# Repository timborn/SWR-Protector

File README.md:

# SWR-Protector
SWR Protection Circuit - cuts power when SWR is too high

This design is from Ron WA7GIL.
He posted it on the QRP Labs forum in early 2023.

V1.0 came back from the fab in May.  Only 2 whitewire fixes.  You
can grab the Gerber and build your own if you don't mind fixing it
when it gets back.

The whitewire changes were solved with a single change to the
schematics, so V1.1 or better of the schematics would be the one
to look at.

V2.0 now includes the "George Option", an optional alarm so you 
can hear when your radio has been shut off by the SWR Protector.

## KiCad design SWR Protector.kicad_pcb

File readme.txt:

Sun Jun 18 12:15:33 MST 2023
----------------------------

My notes to myself about problems, solutions, ideas, questions, ...

1. confirmed: I can use wire between the two BNC connectors and skip coax
2. windings on toroids are both 1:12.  On 1st toroid the center conductor
   passes through once, but then continues to 2nd toroid and loops 12x.
3. OPEN does Ron want to pick a license for this?
4. when we get to calibration step, my guess is something like
   4a. 50 Ohm dummy load, apply pwr and verify it works
   4b. 100 Ohm dummy load (2:1 SWR), apply power and tune pot until it cuts out
5. when the detector fires, the only reset is to power off / power on unit.
   TODO: I can see a need for a power switch to save the barrel plugs some wear
6. we have an LED for BadStuffHappened.  Any value in pwr LED?
7. transformers are just FT37-43 ferrite toroids
8. 1/4 watt resistors are fine. Nothing fancy; 10% tolerance or better is fine
9. Capacitors can be ordinary ceramic discs, 50 volts is sufficient 
10. "Normal" LEDs are 5mm size
11. A common ½W resistor measures about 9.2mm across, 
    while a smaller ¼W resistor is about 6.3mm long.
12. DONE: find a board size that lends itself to a box
    look for Hammond 1590 series die cast aluminum
    I don't think these die cast boxes will do.  Something with faceplates
    will be easier to drill for BNC & barrel jacks, and assemble.
    Ended up using 1593L, which has faceplates and approx size of QDX.
13. DONE: approriate mounting holes for #12 - template provided holes
14. DONE: several parts missing 3D images: barrel jack, relay, DIPs
15. DONE: barrel jack should be replaced with 2-pin variety
    ended up using 3-pin for footprint and model as Ron says that's common
15a. DONE: barrel jack has 3D model
16. DONE: consider V Refl and V Fwd test points coming out on a header
    along with +5 and GND to make micro easier to integrate.
17: RULE: PCB layout on 25 or 50 mils
    "I highly recommend you do not use a grid other than 50 mils
    or 25 mils. Otherwise, there will be tears later. All your
    components, vias, traces and board outlines must be on a 50 or
    25 mil grid. (Silkscreen is a different story)"
    - https://learn.sparkfun.com/tutorials/beginners-guide-to-kicad/all#editing-a-pcb-layout
    0.635mm = 25 mil, 1.27mm = 50 mil  
18: DONE: ground plane fill top layer
19. DONE: when you get ground plane both size add tons of vias
    Good explaination of via stiching techniques: 
    https://www.youtube.com/watch?v=Hp5ngKtl7S4
20. DONE: trace size 1mm; power net 2.5mm
    Fix: (in PCB editor)
    Edit / Select All
    Edit / Edit Track and Via Properties
    Action / Set To Specified Values / Track Width / Track: use netclass width
21. DONE: add a pair of 100 nF caps across LM78L05 +12v/gnd/+5v
22. DONE: switched power should be on same side as transceiver 
23: DONE: junction dot got huge when I added wider traces.
    Fix is File / Schematic Setup / Formatting / Junction dot size: smallest
24. DONE: what is correct placement for barrel jack on edge of board?
25. DONE: what is correct placement for BNC on edge of board?
    keep the silk screen footprint on the board.  Connector will extend out.
26. DONE: orient toroids (transformers) on edge rather than flat
    Found this in someone else's design:
    FT37-43
      <footprint>Inductor_THT:L_Toroid_Vertical_L10.0mm_W5.0mm_P5.08mm
    It only had two pads, but it might form the basis for a custom part.
27. DONE: when it's time to mfgr, review fab specs.  What's "fiducial"?
    Used for SMT, pick & place and inspection tools.
28. DONE: fix warnings about 'footprint does not match copy in library',
    but in the process I lost my 3D models for several parts.  
    Pulled them in again, but the barrel jack is not the correct part
    for those holes (TODO).
29. SOLVED/DONE - when I did a reboot for v0.8 I started with Hammond
    1593L template from DigiKey partners.
    https://github.com/Digi-Key/digikey-partner-kicad-library
    It was that template that also made changes to Board Setup that was
    causing errors with placement of TO-92 package.  DRC was complaining
    that solder mask was too close, and it was implicating the pin
    placement for a very ordinary part.

    After painstaking side-by-side comparison I observe the following 
    changes in (PCB) File / Board Setup:
    - Solder Mask/Paste 
      Solder mask expansion 0.051mm (was 0)
      Solder mask minimum web width 0.25mm (was 0) <-- this is the problem
    - Constraints
      Minimum track width 0.2mm (was 0)
      Minimum via diameter 0.4mm (was 0.5mm)
30. SOLVED/DONE - new via stitching solution.  Download a copy of plugin
    from https://github.com/jsreynaud/kicad-action-scripts
    In PCB tool Tools / External Plugins / Reveal Plugin Folder in Finder
    That's where you put the download.  There's also a Refresh option in 
    there once it's in place.  The rest is easy.  And it works.
31. Send To Fab: zip file with gerber + drill file output
32. SWR Protector BOM.ods is both BOM and cost accounting.
    I'm using Libre Office.  CSV doesn't handle formulas well, 
    and numbers doesn't like naming a cell, for some reason.
33. Git Tag each version and make sure you push tags to origin
    https://git-scm.com/book/en/v2/Git-Basics-Tagging
34. DONE: Ron thinks the power connections should be swapped, end for end, 
    so the power for radio and radio antenna connections come out the same side.
    Is this true?  He says if it's swapped, the relay won't stay triggered.
    THIS WAS ALREADY DONE somewhere between v0.5 and v0.8.  See #22 above.
35. Label the board so the ends are clear.  Everything on LED side goes 
    to radio.
36. 230617 Ron> There is still about a 1 mm gap between the DC connectors 
    and the end caps but it works like this.
    Tim> Dc shifted by 1mm. Noted
    230618 Ron> The DC connectors are close enough now to work fine with 
    the standard depth plugs. No need to move them further out unless 
    making other changes
37. Center BNC on board and make offset to barrel jack identical on both ends.
    I want to be able to create a dilling guide for the end plates.

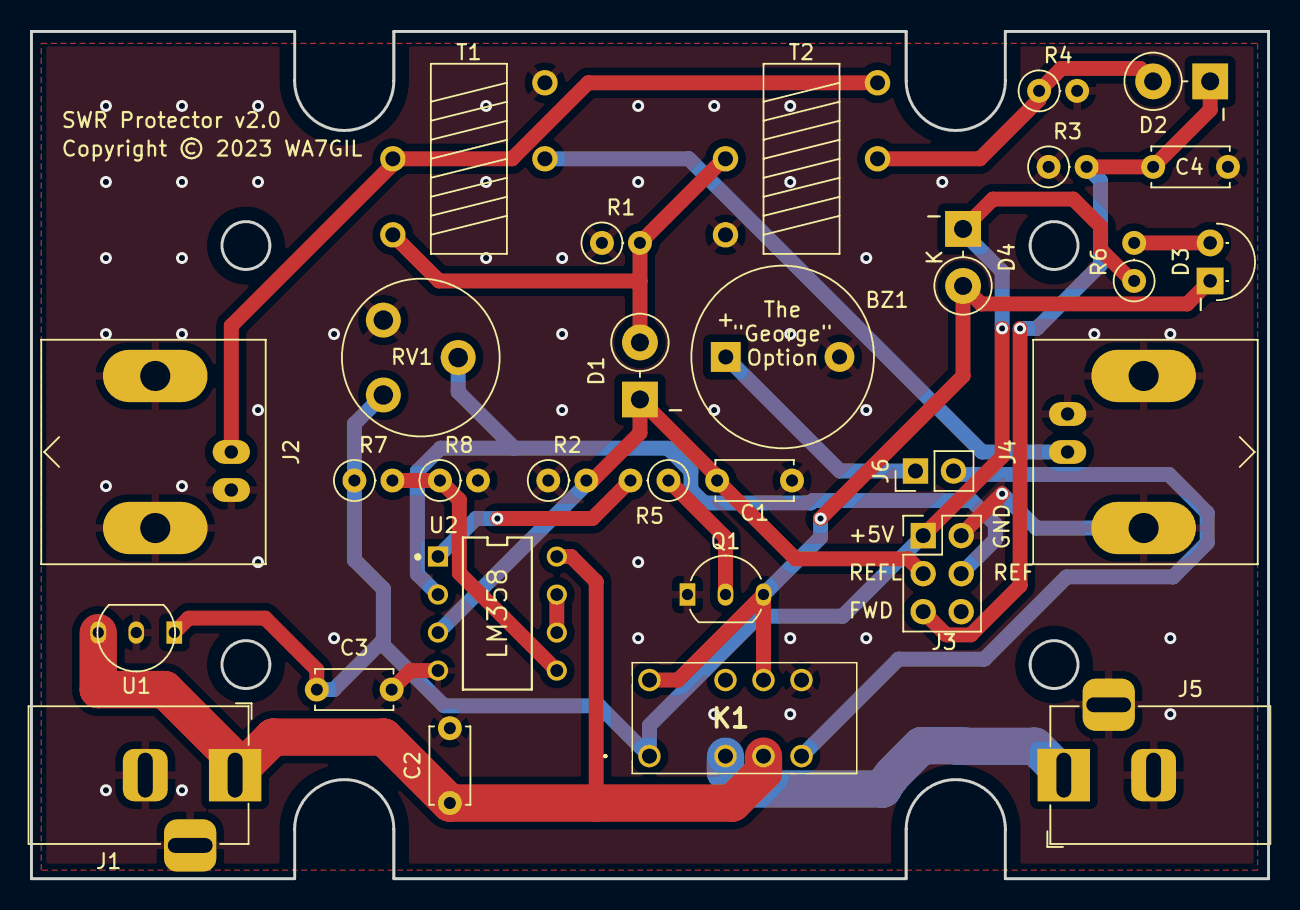
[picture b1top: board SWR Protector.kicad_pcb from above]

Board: 2 copper layers, 82.7 x 56.6 mm, 30 parts (0 on the bottom side), 19 nets.

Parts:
BZ1: Buzzer; Buzzer_12x9.5RM7.6
C1, C4: 10 nF; C_Disc_D5.0mm_W2.5mm_P5.00mm
C2, C3: 100 nF; C_Disc_D5.0mm_W2.5mm_P5.00mm
D1, D2: 1N270; D_DO-15_P3.81mm_Vertical_KathodeUp
D3: red; LED_D5.0mm_Horizontal_O1.27mm_Z9.0mm
D4: 1N4007; D_DO-15_P3.81mm_Vertical_KathodeUp
J1, J5: Barrel_Jack; BarrelJack_Horizontal
J2: antenna; BNC_Amphenol_B6252HB-NPP3G-50_Horizontal
J3: Conn_02x03; PinHeader_2x03_P2.54mm_Vertical
J4: transceiver; BNC_Amphenol_B6252HB-NPP3G-50_Horizontal
J6: Conn_01x02_Pin; PinHeader_1x02_P2.54mm_Vertical
K1: ATX209
Q1: 2N3904; TO-92_Inline
R1, R4: 51R; R_Axial_DIN0207_L6.3mm_D2.5mm_P2.54mm_Vertical
R2, R3: 100K; R_Axial_DIN0207_L6.3mm_D2.5mm_P2.54mm_Vertical
R5: 4K7; R_Axial_DIN0207_L6.3mm_D2.5mm_P2.54mm_Vertical
R6: 1K; R_Axial_DIN0207_L6.3mm_D2.5mm_P2.54mm_Vertical
R7, R8: 10K; R_Axial_DIN0207_L6.3mm_D2.5mm_P2.54mm_Vertical
RV1: 10K; Potentiometer_Piher_PT-10-V05_Vertical
T1, T2: 1:12; FT37-43-TRANSFORMER
U1: LM78L05_TO92; TO-92_Inline
U2: LM358; ON_Semiconductor-626-05-04_2015-P-MFG

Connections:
+5V: C3.1, D4.1 (K), J3.1, K1.1 (+), R6.1, R7.1, RV1.1, U1.1 (VO)
+12V: C2.1, J1.1, K1.4 (COM_1), U1.3 (VI), U2.8 (V+)
GND: BZ1.2 (+), C1.2, C2.2, C3.2, C4.2, J1.2, J1.3, J2.2 (Ext), J3.2, J4.2 (Ext), J5.2, J5.3, K1.8 (NO_2), Q1.1 (E), R1.1, R2.1, R3.1, R4.2, R8.2, RV1.3, T1.1 (AA), T2.2 (AB), U1.2 (GND), U2.4 (V-)
unnamed: BZ1.1 (-), J6.1
unnamed: D1.2 (A), R1.2, T1.2 (AB), T2.4 (SB)
unnamed: C1.1, D1.1 (K), J3.3, R2.2, U2.3 (+)
unnamed: D2.2 (A), R4.1, T2.3 (SA)
unnamed: C4.1, D2.1 (K), J3.5, R3.2
unnamed: D3.2 (A), R6.2
unnamed: D3.1 (K), D4.2 (A), K1.9 (COM_2), K1.12 (-), Q1.3 (C)
unnamed: J2.1 (In), T1.4 (SB), T2.1 (AA)
unnamed: J3.4, RV1.2, U2.2 (-)
unnamed: J4.1 (In), T1.3 (SA)
unnamed: J6.2, K1.5 (NO_1)
unnamed: J5.1, K1.3 (NC_1)
unnamed: Q1.2 (B), R5.1
unnamed: R5.2, U2.1
unnamed: R7.2, R8.1, U2.5 (+)
unnamed: U2.6 (-), U2.7

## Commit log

2023-05-07 initial commit v0.3
    Swapped out Fujitsu relay for Panasonic ATX209 which switches much faster.
    Representing coax inductors as transformers. Not clear if that is correct.
    Still need to add missing 78LM05 regulator.
2023-05-07 v0.4 swapped relay for Panasonic. Much faster switching. Reworked +5V ckt.
2023-05-07 updated README.md with a pointer to Ron
2023-05-07 1. voltage divider in place 2. > Couple issues with the schematic... the base of Q1 is shown going through the transistor to its own collector. That connection should be removed. Good eyes. That's an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
2023-05-08 added notes for myself, started PCB layout and updated gitignore to ignore some Mac crap
2023-05-09 placed parts on PCB and wired them up. DRC reports zero errors and a handful of warnings about overlapping silk screen.
2023-05-09 After review with Ron, lots of changes to make. Updates readme.txt with lots of notes TODO. Started playing with net classes as I need wider traces. 1mm for default trace, and 2.5mm for +12v power tr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
2023-05-09 Wider traces done. FT37-43 oriented vertically with new footprint.
2023-05-09 moved transceiver BNC jack to the same side of the board as the switched pwr
2023-05-09 Added a couple of caps on the 5V regulator.
2023-05-09 added 3D model for ATX209 relay
2023-05-10 found 3D model for BNC rt angle. Looks good; doesn't match the holes.
2023-05-10 updated BNC to something reasonable, w/ Ron\'s help
2023-05-10 changed footprint for BNC, barrel connectors to make them normal
2023-05-10 added mounting holes; checkpoint progress on footprints for connectors
2023-05-10 added header for pwr/gnd and both fwd and rev for microcontroler
2023-05-10 added header pins; fixed some bugs
2023-05-10 Added ground plane on face layer. Fixed broken 3D models.
2023-05-11 learned how to do via stitching, but the array lands over everything so I spent a lot of time finding and fixing errors (ground via punching right thru power trace, for instance). Next time the via s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
2023-05-11 v0.8 massive changes. Start with 1593L board, imported schematic, updated symbol libs and footprint libs. Working on layout now. Dropped testpoints as we have them on the header now. Diodes and resis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
2023-05-11 checked off 12 & 13 on TODO list - using 1593L footprint now
2023-05-11 checkpoint progress on board layout
2023-05-12 Starting with Hammond template broke DRC. Found/fixed those issues.
2023-05-12 resolved all DRC errors and warnings Changed silkscreen for LED that was sticking off the edge. Wrestled with GND pad that wanted 2 thermal relief but could only get 1 because I had routed a PWR trac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
2023-05-12 Set board minimums to at least PCBWAY and JLCPCB (I hope). DRC passes.
2023-05-12 new day, new version number v0.9
2023-05-12 LM358 was getting solder mask all over holes. Fixed. I think this has to do with an edit I made to one of the holes to allow two thermal traces. Somehow when I edited it, F.Mask and B.Mask were unsel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
    Also added 3D for LM358 and ATX209.
2023-05-12 v1.0 final silk screen, via stitching, lots of squinting sending off to fab
2023-05-12 last notes during sending off to fab
2023-05-21 added a 3D rendering of v1.0 board
2023-05-21 found 3D models for barrel jacks and BNC connectors so the 3D renders nicely
2023-05-26 pictures of V1.0 board arriving, built and verified. IT WORKS
2023-05-26 start working on V2.0
2023-05-26 added photos of V1.0 in a case (both ends)
2023-05-27 really rough assembly instructions for V1.0
2023-05-27 updated V2 Changelog
2023-05-27 checkpoint changes working on V2.0
2023-05-27 completed everything on the list of requested changes in V2-Changelog.txt. Passes DRC, but we get warnings for things like silkscreen off the edge of the board (deliberate, for the power connectors).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
2023-05-27 started basic cost accounting using BOM
2023-05-27 v1.2 - added pins 2 & 3 from LM358 to header
2023-05-28 checkpoint changes made late satuday that i cannot remember what i did
2023-05-28 Removed pin 6 on header. Fine tune footprint for Q1. Realizing pin 6 on header just duplicated the VReflected voltage already on pin 3, I made pin 6 NC. Fiddled with footprint for Q1 to try to remove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
2023-05-28 created Fab Checklist so I do not forget things
2023-05-28 The George Option complete. George asked for a buzzer when relay trips. Used 12V part w/ same footprint. That thing is HUGE. I can see already I want a jumper to disable it after I build one to test.
2023-05-28 add jumper to disable George buzzer
2023-05-28 Change 10K trimpot from Bourne to PT10. Different pinout, vastly cheaper. Started picking up a warning about copper slivers. Found one that was an acute wedge, so I widened the trace to slop over it.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
2023-05-28 Update BOM. Using new RV1. Two sliver warnings are back. Rerouted and picked up the two slivers I had previous eliminated. Updated BOM with missing parts. Updated price for new RV1.
2023-05-29 update BOM with revised parts & prices
2023-05-29 V2.0 sent off to the fab. Updates all over the place, mostly version number. Updated BOM with a more realistic price for PCBs after the newbie discont disappeared. Still, $30 for 5 boards is pretty g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
    > Ron Taylor, 46 min
    > Consider it “Blessed”
2023-05-30 updated FAB checklist
2023-05-30 made a note to tag versions in git
2023-05-30 noted that PCBWAY charges more for mask color other than green
2023-06-16 Ron wants the power connectors swapped end for end
2023-06-17 added records of schematic and PCB at v1.0 and original sketch
2023-06-18 updated readme - connectors look to be on correct sides and barrel jack should move 1mm closer to edge of board next time
2023-06-18 ron is vacillating about moving the barrel jack
2023-06-18 next time, center BNC on board and make offset to barrel jack identical
2023-12-02 typo
2023-12-05 updated photos of V1.x

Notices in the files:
SWR Protector.kicad_pcb:
Copyright © 2023 WA7GIL
